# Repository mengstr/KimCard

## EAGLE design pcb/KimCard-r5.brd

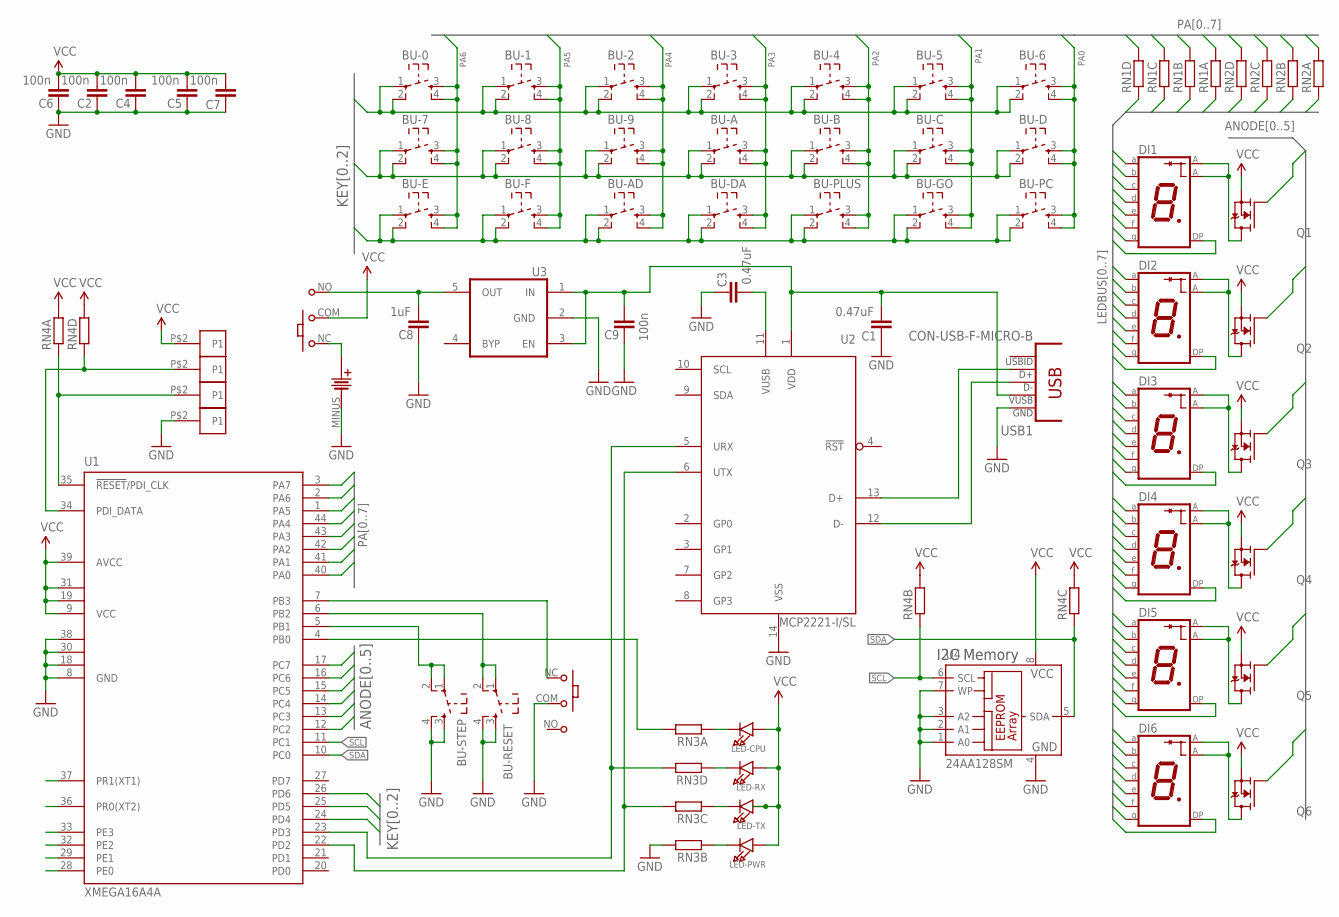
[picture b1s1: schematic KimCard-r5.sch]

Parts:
BA1: BATTERY-3V; AAAX2
BU-0, BU-1, BU-2, BU-3, BU-4, BU-5, BU-6, BU-7, BU-8, BU-9: SW_TACT_4P; SW_TACT_SMALL
BU-A: SW_TACT_4P; SW_TACT_SMALL
BU-AD: SW_TACT_4P; SW_TACT_SMALL
BU-B: SW_TACT_4P; SW_TACT_SMALL
BU-C: SW_TACT_4P; SW_TACT_SMALL
BU-D: SW_TACT_4P; SW_TACT_SMALL
BU-DA: SW_TACT_4P; SW_TACT_SMALL
BU-E: SW_TACT_4P; SW_TACT_SMALL
BU-F: SW_TACT_4P; SW_TACT_SMALL
BU-GO: SW_TACT_4P; SW_TACT_SMALL
BU-PC: SW_TACT_4P; SW_TACT_SMALL
BU-PLUS: SW_TACT_4P; SW_TACT_SMALL
BU-RESET: SW_TACT_4P; SW_TACT_SMALL
BU-STEP: SW_TACT_4P; SW_TACT_SMALL
C1, C3: 0.47uF; 0805
C2, C4, C5, C6, C7, C9: 100n; 0805
C8: 1uF; 0805
DI1, DI2, DI3, DI4, DI5, DI6: 7SEG-CA2; KCSA03
LED-CPU: LEDSMD0805; CHIPLED_0805
LED-PWR: LEDSMD0805; CHIPLED_0805
LED-RX: LEDSMD0805; CHIPLED_0805
LED-TX: LEDSMD0805; CHIPLED_0805
PDI-CLK: PAD-2X3; PAD2X3
PDI-DATA: PAD-2X3; PAD2X3
PDI-GND: PAD-2X3; PAD2X3
PDI-VCC: PAD-2X3; PAD2X3
Q1, Q2, Q3, Q4, Q5, Q6: TRANSISTOR_FET_BS170-SOT-23; SOT-23
RN1, RN2, RN3, RN4: RESISTOR_ARRAY_4; RN8P-4R-CRA06S
U1: XMEGA16A4A; TQFP44
U2: MCP2221-I/SL; SOIC14
U3: VREG_5PINS-SOT-23-5; SOT-23-5
U4: 24AA128SM; SO-08M
U$1, U$2: SLIDESWITCHPCM12SMTR; PCM12SMTR
USB1: CON-USB-F-MICRO-B; CONN_USB_MICRO-B

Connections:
BAT: BA1.PLUS, U$1.NC
CPU: RN3.8 (2), U1.4 (PB0)
GND: BA1.MINUS, BU-RESET.3, BU-RESET.4, BU-STEP.3, BU-STEP.4, C1.1, C2.1, C3.1, C4.1, C5.1, C6.1, C7.1, C8.1, C9.1, PDI-GND.P$2, RN3.7 (2), U1.8 (GND), U1.18 (GND1), U1.30 (GND2), U1.38 (GND3), U2.14 (VSS), U3.2 (GND), U4.1 (A0), U4.2 (A1), U4.3 (A2), U4.4 (GND), U4.7 (WP), U$2.COM, USB1.P5 (GND)
KEYROW0: BU-0.1, BU-0.2, BU-1.1, BU-1.2, BU-2.1, BU-2.2, BU-3.1, BU-3.2, BU-4.1, BU-4.2, BU-5.1, BU-5.2, BU-6.1, BU-6.2, U1.24 (PD4)
KEYROW1: BU-7.1, BU-7.2, BU-8.1, BU-8.2, BU-9.1, BU-9.2, BU-A.1, BU-A.2, BU-B.1, BU-B.2, BU-C.1, BU-C.2, BU-D.1, BU-D.2, U1.25 (PD5)
KEYROW2: BU-AD.1, BU-AD.2, BU-DA.1, BU-DA.2, BU-E.1, BU-E.2, BU-F.1, BU-F.2, BU-GO.1, BU-GO.2, BU-PC.1, BU-PC.2, BU-PLUS.1, BU-PLUS.2, U1.26 (PD6)
LEDBUS0: DI1.P$7 (A), DI2.P$7 (A), DI3.P$7 (A), DI4.P$7 (A), DI5.P$7 (A), DI6.P$7 (A), RN2.1
LEDBUS1: DI1.P$6 (B), DI2.P$6 (B), DI3.P$6 (B), DI4.P$6 (B), DI5.P$6 (B), DI6.P$6 (B), RN2.2 (1)
LEDBUS2: DI1.P$4 (C), DI2.P$4 (C), DI3.P$4 (C), DI4.P$4 (C), DI5.P$4 (C), DI6.P$4 (C), RN2.3 (1)
LEDBUS3: DI1.P$2 (D), DI2.P$2 (D), DI3.P$2 (D), DI4.P$2 (D), DI5.P$2 (D), DI6.P$2 (D), RN2.4 (1)
LEDBUS4: DI1.P$1 (E), DI2.P$1 (E), DI3.P$1 (E), DI4.P$1 (E), DI5.P$1 (E), DI6.P$1 (E), RN1.1
LEDBUS5: DI1.P$9 (F), DI2.P$9 (F), DI3.P$9 (F), DI4.P$9 (F), DI5.P$9 (F), DI6.P$9 (F), RN1.2 (1)
LEDBUS6: DI1.P$10 (G), DI2.P$10 (G), DI3.P$10 (G), DI4.P$10 (G), DI5.P$10 (G), DI6.P$10 (G), RN1.3 (1)
LEDBUS7: DI1.P$5 (DP), DI2.P$5 (DP), DI3.P$5 (DP), DI4.P$5 (DP), DI5.P$5 (DP), DI6.P$5 (DP), RN1.4 (1)
LEDCA0: Q1.1 (G), U1.12 (PC2)
LEDCA1: Q2.1 (G), U1.13 (PC3)
LEDCA2: Q3.1 (G), U1.14 (PC4)
LEDCA3: Q4.1 (G), U1.15 (PC5)
LEDCA4: Q5.1 (G), U1.16 (PC6)
LEDCA5: Q6.1 (G), U1.17 (PC7)
unnamed: RN3.5 (2), U1.23 (PD3), U2.5 (URX)
unnamed: LED-RX.C, RN3.4 (1)
unnamed: U2.13 (D+), USB1.P3 (D+)
unnamed: U2.12 (D-), USB1.P2 (D-)
unnamed: C3.2, U2.11 (VUSB)
unnamed: RN3.6 (2), U1.22 (PD2), U2.6 (UTX)
unnamed: LED-TX.C, RN3.3 (1)
unnamed: C8.2, U3.5 (OUT), U$1.NO
unnamed: LED-PWR.C, RN3.2 (1)
unnamed: LED-CPU.C, RN3.1
PA0: BU-6.3, BU-6.4, BU-D.3, BU-D.4, BU-PC.3, BU-PC.4, RN2.8 (2), U1.40 (PA0)
PA1: BU-5.3, BU-5.4, BU-C.3, BU-C.4, BU-GO.3, BU-GO.4, RN2.7 (2), U1.41 (PA1)
PA2: BU-4.3, BU-4.4, BU-B.3, BU-B.4, BU-PLUS.3, BU-PLUS.4, RN2.6 (2), U1.42 (PA2)
PA3: BU-3.3, BU-3.4, BU-A.3, BU-A.4, BU-DA.3, BU-DA.4, RN2.5 (2), U1.43 (PA3)
PA4: BU-2.3, BU-2.4, BU-9.3, BU-9.4, BU-AD.3, BU-AD.4, RN1.8 (2), U1.44 (PA4)
PA5: BU-1.3, BU-1.4, BU-8.3, BU-8.4, BU-F.3, BU-F.4, RN1.7 (2), U1.1 (PA5)
PA6: BU-0.3, BU-0.4, BU-7.3, BU-7.4, BU-E.3, BU-E.4, RN1.6 (2), U1.2 (PA6)
PA7: RN1.5 (2), U1.3 (PA7)
PDI_CLOCK: PDI-CLK.P$2, RN4.1, U1.35 (!RESET!/PDI_CLK)
PDI_DATA: PDI-DATA.P$2, RN4.4 (1), U1.34 (PDI_DATA)
PE0: U1.28 (PE0)
PE1: U1.29 (PE1)
PE2: U1.32 (PE2)
PE3: U1.33 (PE3)
PR1: U1.37 (PR1(XT1))
PR2: U1.36 (PR0(XT2))
Q1C: DI1.P$3 (A), DI1.P$8 (A), Q1.3 (D)
Q2C: DI2.P$3 (A), DI2.P$8 (A), Q2.3 (D)
Q3C: DI3.P$3 (A), DI3.P$8 (A), Q3.3 (D)
Q4C: DI4.P$3 (A), DI4.P$8 (A), Q4.3 (D)
Q5C: DI5.P$3 (A), DI5.P$8 (A), Q5.3 (D)
Q6C: DI6.P$3 (A), DI6.P$8 (A), Q6.3 (D)
RSET: BU-RESET.1, BU-RESET.2, U1.6 (PB2)
SCL: RN4.2 (1), U1.11 (PC1), U4.6 (SCL)
SDA: RN4.3 (1), U1.10 (PC0), U4.5 (SDA)
SST: U1.7 (PB3), U$2.NC
STEP: BU-STEP.1, BU-STEP.2, U1.5 (PB1)
VCC: C2.2, C4.2, C5.2, C6.2, C7.2, LED-CPU.A, LED-PWR.A, LED-RX.A, LED-TX.A, PDI-VCC.P$2, Q1.2 (S), Q2.2 (S), Q3.2 (S), Q4.2 (S), Q5.2 (S), Q6.2 (S), RN4.5 (2), RN4.6 (2), RN4.7 (2), RN4.8 (2), U1.9 (VCC), U1.19 (VCC1), U1.31 (VCC2), U1.39 (AVCC), U4.8 (VCC), U$1.COM
VUSB: C1.2, C9.2, U2.1 (VDD), U3.1 (IN), U3.3 (EN), USB1.P1 (VUSB)

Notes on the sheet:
I2C Memory

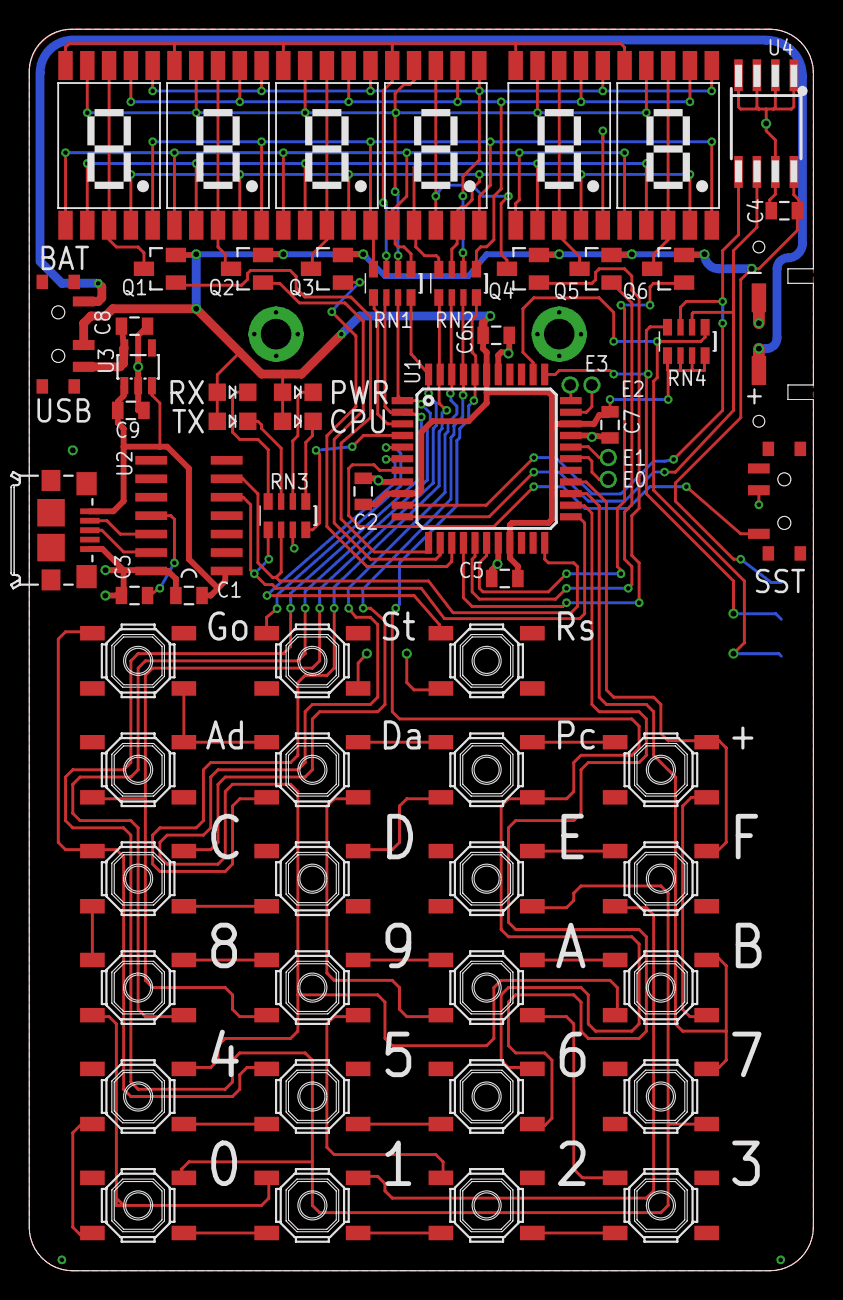
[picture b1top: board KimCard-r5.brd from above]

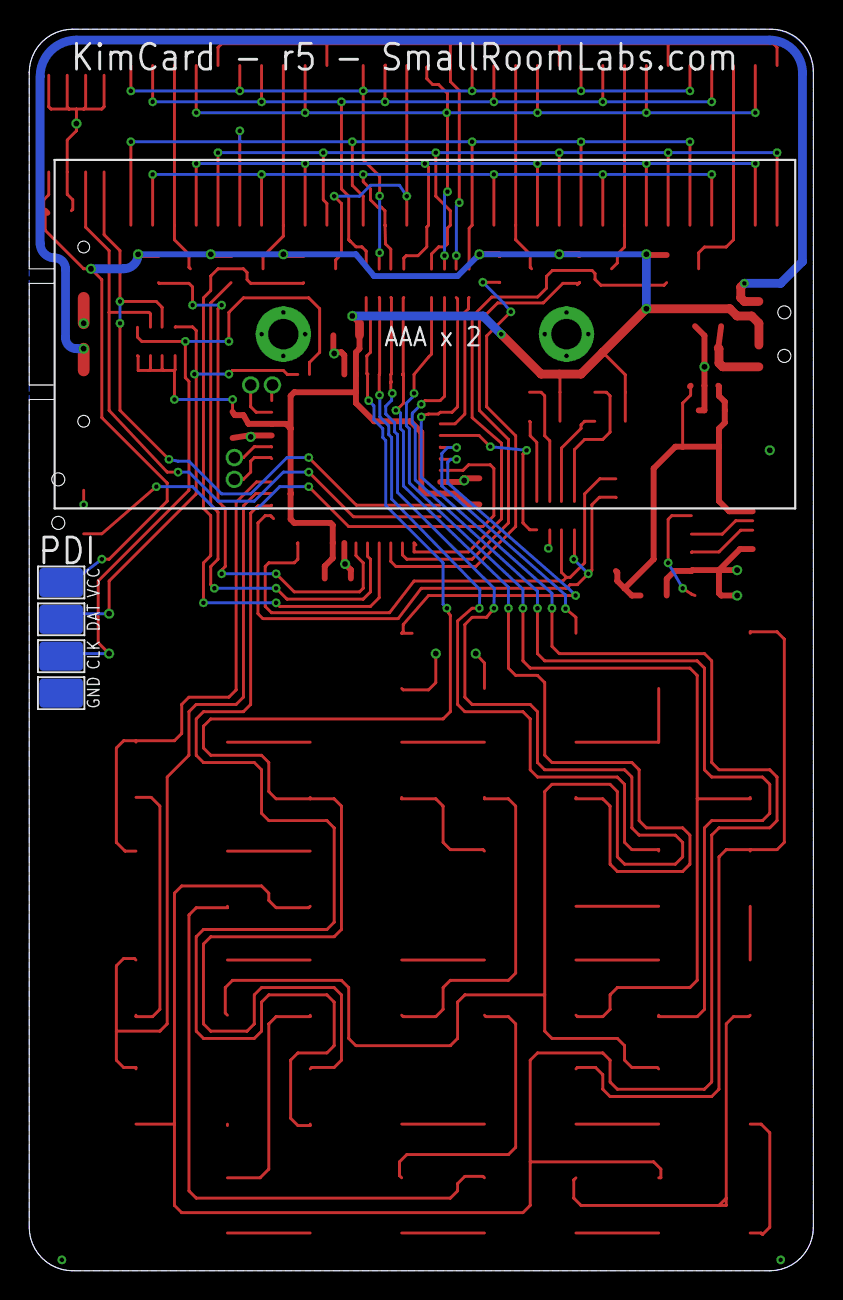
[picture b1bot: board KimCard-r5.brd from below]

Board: 2 copper layers, 54.0 x 85.5 mm, 65 parts (5 on the bottom side), 53 nets.

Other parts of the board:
U$7: SRL-LOGO-STOP-5MM

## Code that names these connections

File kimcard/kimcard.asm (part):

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;
; ATMEGA644 PORT				USED FOR 
; -------------------------		----------------------------
; PB0 (PCINT0/CLKO/ICP1)
; PB1 (OC1A/PCINT1)
; PB2 (SS/OC1B/PCINT2)
; PB3 (MOSI/OC2A/PCINT3)
; PB4 (MISO/PCINT4)
; PB5 (SCK/PCINT5)
; PB6 (PCINT6/XTAL1/TOSC1)		(AVR XTAL)
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;
; PD0 (PCINT16/RXD) 			6502 Port A0 - LED Segment A
; PD1 (PCINT17/TXD) 			6502 Port A1 - LED Segment B
; PD2 (PCINT18/INT0)			6502 Port A2 - LED Segment C
; PD3 (PCINT19/OC2B/INT1)		6502 Port A3 - LED Segment D
; PD4 (PCINT20/XCK/T0)			6502 Port A4 - LED Segment E
; PD5 (PCINT21/OC0B/T1)			6502 Port A5 - LED Segment F
; PD6 (PCINT22/OC0A/AIN0)		6502 Port A6 - LED Segment G
; PD7 (PCINT23/AIN1)			
;
; PC0 (ADC0/PCINT8)				6502 Port - LED Digit 1
; PC1 (ADC1/PCINT9)				6502 Port - LED Digit 2
; PC2 (ADC2/PCINT10)			6502 Port - LED Digit 3
; PC3 (ADC3/PCINT11)			6502 Port - LED Digit 4
; PC4 (ADC4/SDA/PCINT12)		6502 Port - LED Digit 5
; PC5 (ADC5/SCL/PCINT13)		6502 Port - LED Digit 6
; PC6 (PCINT14/RESET) 			(AVR RESET/DW)
;

;
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
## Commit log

2011-03-01 Eagle PCB files added
2011-03-01 Changed to AVRstudio5
2011-03-02 Split source to .inc-files. Added 6502 opcode test functionalities
2011-03-02 Opcode fetch fixed to use correct SRAM page
2011-03-03 Added .gitignore
2011-03-03 Added /NODELAY to clean.cmd -files
2011-03-06 Added 6502.exe assembler/simulator
2011-03-06 Page fixing code as a macro
2012-06-27 Renamed orginal Mega644 PCB to v1
2012-06-27 Routed XMEGA version of the board
2012-06-27 Some dox added
2012-06-28 Minor touchups on layout
2012-10-25 Updated firmware for ATXMEGA32D4
2012-10-25 Removed .inc from .gitignore
2012-10-25 Final version of V2 board & Gerbers
2012-10-25 Added MOS logo for pcb backside
2012-10-25 Cleaned up deleted files
2012-10-25 Routing incomplete. Changed to SMD displays. Fixed button swaps.
2012-10-26 More routing. Added FT201 as USB option.
2012-10-26 More routing.
2012-10-26 New labels
2012-10-27 Everything routed
2012-10-27 Files for 6502 Cheat Sheet
2012-10-27 Fixed part labels
2012-10-27 Final routing & fixes for GND/VCC
2012-10-28 Fixed CMP emulation by inverting Carry after the CP-instruction
2012-10-28 Added more extentions to .gitignore
2012-11-28 Rearanged code & files a bit
2012-11-28 More file reorganizations
2012-11-28 Pictures for readme.md
2012-11-28 Removed old AvrStudio4 folder
2015-04-24 Update before continuing on this project
2015-05-01 All parts on top
2015-05-03 Rev 5 almost finalized. Needs silk tuneups

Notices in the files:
parts and their libraries:
SmallRoomLabs: Copyright(c) 2011 Mats Engstrom - mats@smallroomlabs.com
SmallRoomLabs: http://creativecommons.org/licenses/by-sa/3.0
SmallRoomLabs: STANDARD FRAME w. Copyright & License info
